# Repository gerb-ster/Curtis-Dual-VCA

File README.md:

# Curtis-Dual-VCA

A dual VCA module based on the CEM 3360 IC

## Status: Finished

- done: first schematic & board design
- done: breadboard and test
- done: design frontpanel
- done: order PCB and build prototype

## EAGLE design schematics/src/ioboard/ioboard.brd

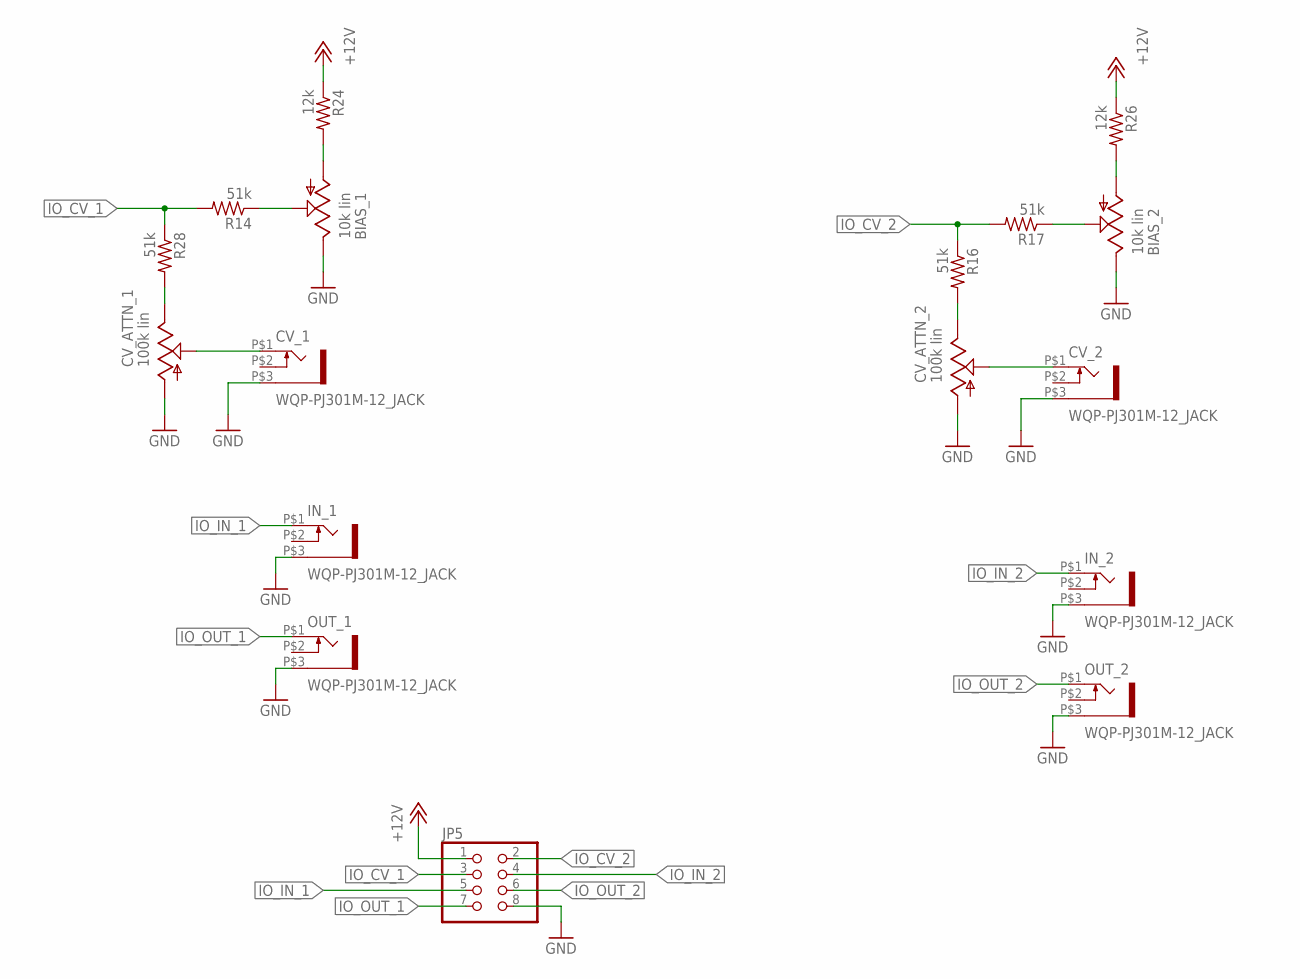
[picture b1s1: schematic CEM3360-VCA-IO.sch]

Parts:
BIAS_1, BIAS_2: 10k lin; EVUF
CV_1, CV_2: WQP-PJ301M-12_JACK
CV_ATTN_1, CV_ATTN_2: 100k lin; EVUF
IN_1, IN_2: WQP-PJ301M-12_JACK
JP5: PINHD-2X4; 2X04
OUT_1, OUT_2: WQP-PJ301M-12_JACK
R14, R16, R17, R28: 51k; 0207/7
R24, R26: 12k; 0207/7

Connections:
+12V: JP5.1, R24.1, R26.1
GND: BIAS_1.3 (E), BIAS_2.3 (E), CV_1.P$3 (1), CV_2.P$3 (1), CV_ATTN_1.1 (A), CV_ATTN_2.1 (A), IN_1.P$3 (1), IN_2.P$3 (1), JP5.8, OUT_1.P$3 (1), OUT_2.P$3 (1)
IO_CV_1: JP5.3, R14.2, R28.1
IO_CV_2: JP5.2, R16.1, R17.2
IO_IN_1: IN_1.P$1 (2), JP5.5
IO_IN_2: IN_2.P$1 (2), JP5.4
IO_OUT_1: JP5.7, OUT_1.P$1 (2)
IO_OUT_2: JP5.6, OUT_2.P$1 (2)
unnamed: CV_ATTN_1.3 (E), R28.2
unnamed: BIAS_1.2 (S), R14.1
unnamed: BIAS_1.1 (A), R24.2
unnamed: CV_1.P$1 (2), CV_ATTN_1.2 (S)
unnamed: CV_ATTN_2.3 (E), R16.2
unnamed: CV_2.P$1 (2), CV_ATTN_2.2 (S)
unnamed: BIAS_2.2 (S), R17.1
unnamed: BIAS_2.1 (A), R26.2

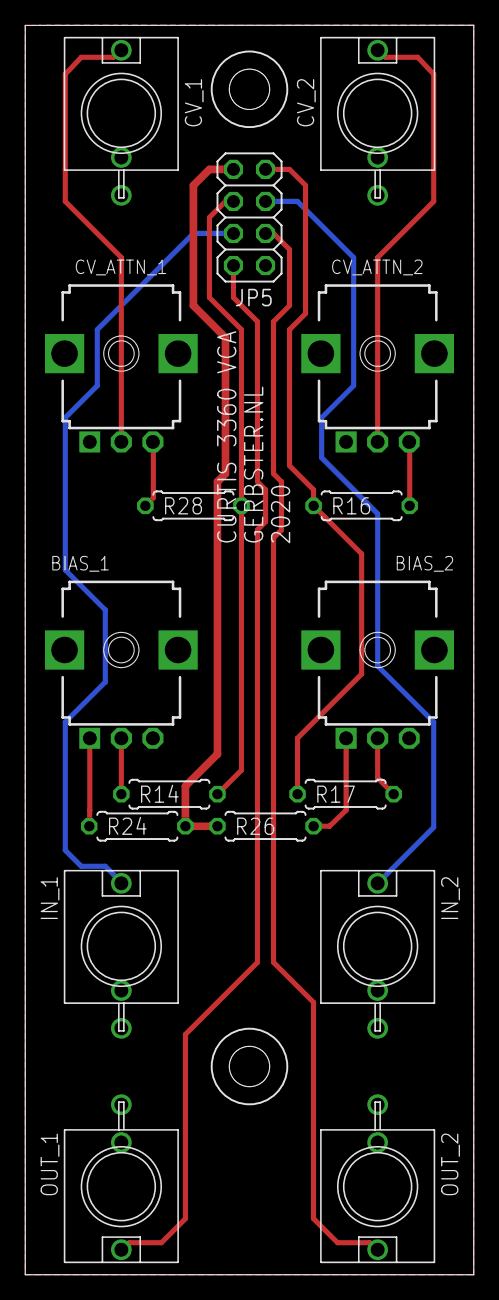
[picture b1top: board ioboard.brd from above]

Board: 2 copper layers, 35.6 x 99.1 mm, 17 parts (0 on the bottom side), 16 nets.

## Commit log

2021-05-01 done
2021-05-01 added .gitignore files
2021-05-07 added files & structure
2021-05-10 Added Status
2021-05-11 Added Status & Images
2021-06-15 Updated Schematics, Fixed Power Socket orientation
2021-08-06 Updated some schematics and docs
2021-08-10 Fixed some bugs and updated documentation
2022-04-20 Some updates & bugfixes
2022-04-22 Fixed schematics & descriptions
2022-05-17 Updated Firmware
2022-05-18 Updated Faceplates
2022-05-18 Fixed issues
2022-05-21 Fixed schematics
2022-05-28 General updates
